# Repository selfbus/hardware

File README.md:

<h2>Deprecation Notice</h2>
Until May 11th 2023 selfbus hardware was split into "hardware" (stable projects) and "hardware-incubation" (dev projects). Since this split constantly lead to confusion mainly because stable hardware was not migrated to "hardware" but also because namings and structures differed between these two repositories, we decided to re-structe both to the same folder structure and merge them. In combination with clear collaboration rules it should be much easier now to understand what can be found where. 
<br/><br/>The newly created repository is located here: https://github.com/selfbus/hardware-merged

<hr/>

<h2>Master-Branch</h2>
This branch contains released Selfbus hardware

The top level directories contain:

<ul>
<li> Apps - applications/devices that require a controller board
<li> Controller - controller boards
<li> Module - devices that do not require a controller board
<li> Misc - other stuff that is not an EIB bus device
</ul>

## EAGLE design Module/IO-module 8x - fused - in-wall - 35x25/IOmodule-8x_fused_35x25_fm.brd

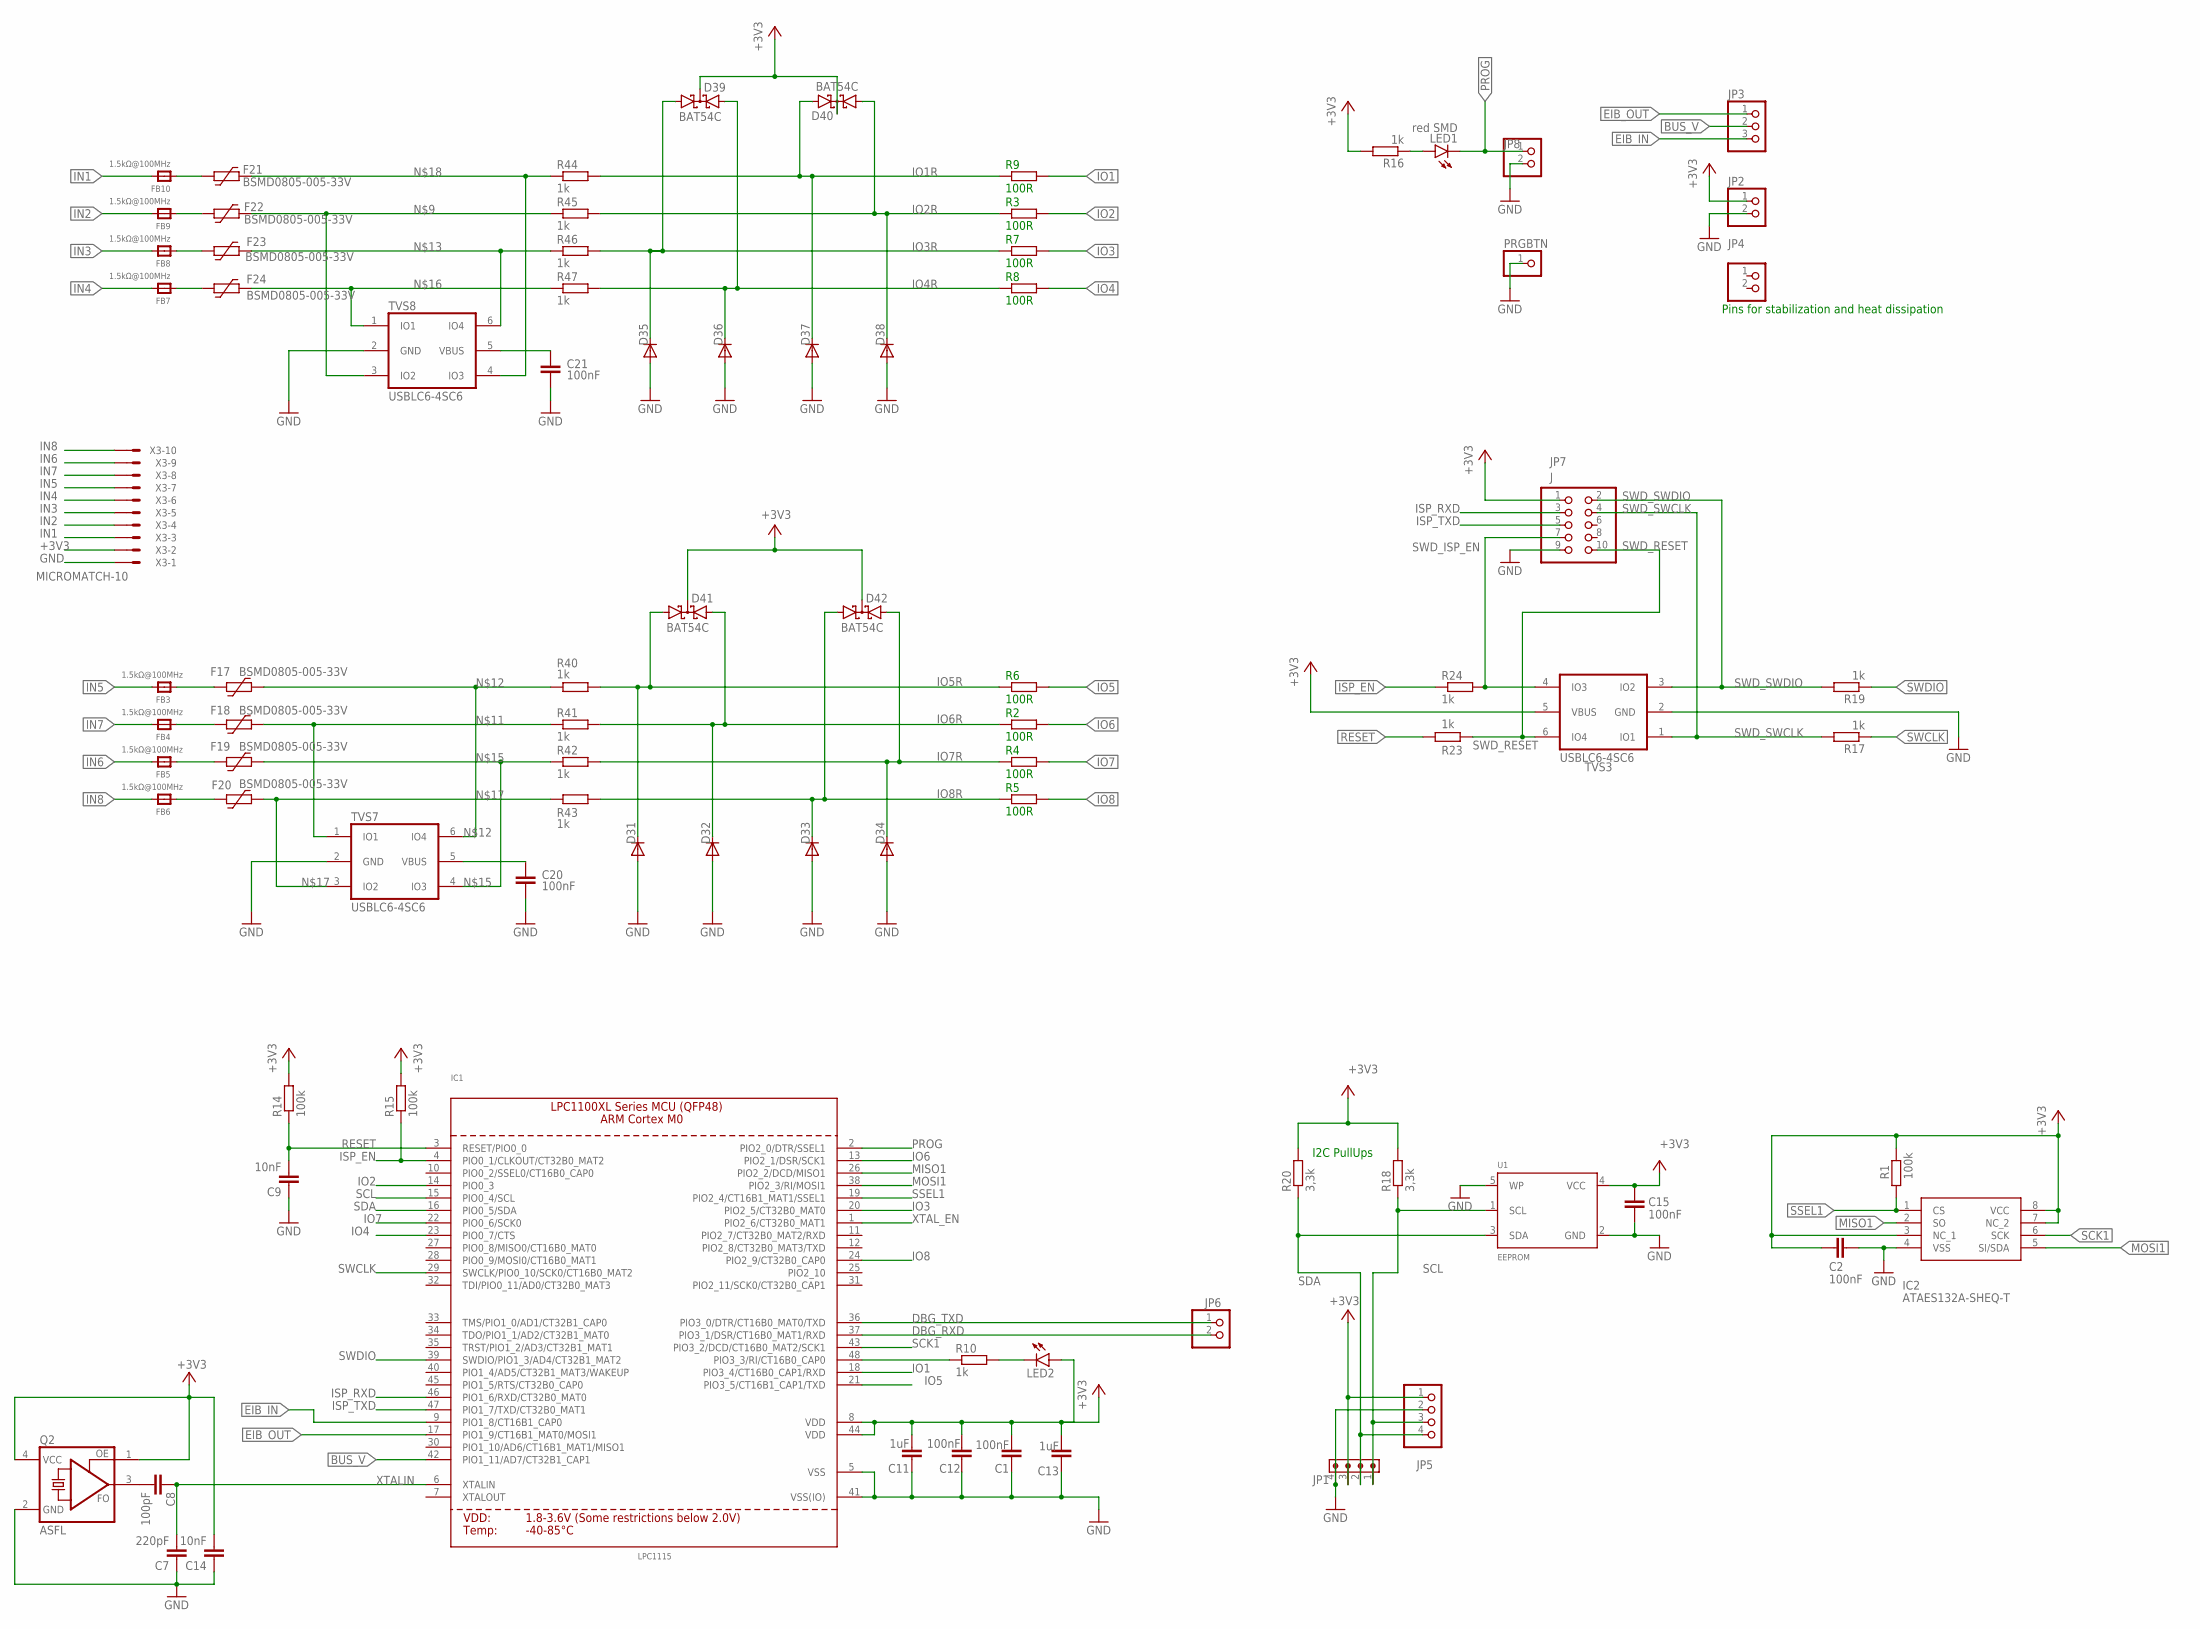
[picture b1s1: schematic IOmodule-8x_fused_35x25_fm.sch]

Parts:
C1, C2, C12, C15, C20, C21: 100nF; C0805
C7: 220pF; C0805
C8: 100pF; C0805
C9, C14: 10nF; C0805
C11, C13: 1uF; C0805
D31, D32, D33, D34, D35, D36, D37, D38: DDZ9684; SOD-123
D39, D40, D41, D42: BAT54C; SOT23
F17, F18, F19, F20, F21, F22, F23, F24: BSMD0805-005-33V; 0805L
FB3, FB4, FB5, FB6, FB7, FB8, FB9, FB10: 1.5kΩ@100MHz; 0805
IC1: LPC1115; LQFP48
IC2: ATAES132A-SHEQ-T; SOIC127P600X175-8N
JP1: 62000411622
JP2, JP4, JP6, JP8: PINHD-1X2; 1X02
JP3: PINHD-1X3; 1X03
JP5: PINHD-1X4; 1X04
JP7: J; 2X05M
LED1: red SMD; CHIPLED_0805
LED2: LEDCHIPLED_0805; CHIPLED_0805
PRGBTN: PINHD-1X1; 1X01
Q2: ASFL; ASF
R1, R14, R15: 100k; R0805
R2, R3, R4, R5, R6, R7, R8, R9: 100R; R0805
R10, R16, R17, R19, R23, R24, R40, R41, R42, R43, R44, R45, R46, R47: 1k; R0805
R18, R20: 3,3k; R0805
TVS3, TVS7, TVS8: USBLC6-4SC6; SOT-23-6L
U1: EEPROM; SOT23-5
X3: MICROMATCH-10

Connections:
+3V3: C1.2, C2.1, C11.2, C12.2, C13.2, C14.2, C15.1, D39.3 (CC), D40.3 (CC), D41.3 (CC), D42.3 (CC), IC1.8 (VDD), IC1.44 (VDD), IC2.3 (NC_1), IC2.7 (NC_2), IC2.8 (VCC), JP1.3, JP2.1, JP5.1, JP7.1, LED2.A, Q2.1 (OE), Q2.4 (VCC), R1.2, R14.2, R15.2, R16.2, R18.2, R20.2, TVS3.5 (VBUS), U1.4 (VCC), X3.2
BUS_V: IC1.42 (PIO1_11/AD7/CT32B1_CAP1), JP3.2
DBG_RXD: IC1.37 (PIO3_1/DSR/CT16B0_MAT1/RXD), JP6.2
DBG_TXD: IC1.36 (PIO3_0/DTR/CT16B0_MAT0/TXD), JP6.1
EIB_IN: IC1.9 (PIO1_8/CT16B1_CAP0), JP3.3
EIB_OUT: IC1.17 (PIO1_9/CT16B1_MAT0/MOSI1), JP3.1
GND: C1.1, C2.2, C7.1, C9.1, C11.1, C12.1, C13.1, C14.1, C15.2, C20.1, C21.1, D31.A, D32.A, D33.A, D34.A, D35.A, D36.A, D37.A, D38.A, IC1.5 (VSS), IC1.41 (VSS(IO)), IC2.4 (VSS), JP1.4, JP2.2, JP5.2, JP7.9, JP8.2, PRGBTN.1, Q2.2 (GND), TVS3.2 (GND), TVS7.2 (GND), TVS8.2 (GND), U1.2 (GND), U1.5 (WP), X3.1
IN1: FB10.2, X3.3
IN2: FB9.2, X3.4
IN3: FB8.2, X3.5
IN4: FB7.2, X3.6
IN5: FB3.2, X3.7
IN6: FB5.2, X3.9
IN7: FB4.2, X3.8
IN8: FB6.2, X3.10
IO1: IC1.18 (PIO3_4/CT16B0_CAP1/RXD), R9.2
IO1R: D37.C, D40.2 (A2), R9.1, R44.2
IO2: IC1.14 (PIO0_3), R3.2
IO2R: D38.C, D40.1 (A1), R3.1, R45.2
IO3: IC1.20 (PIO2_5/CT32B0_MAT0), R7.2
IO3R: D35.C, D39.1 (A1), R7.1, R46.2
IO4: IC1.23 (PIO0_7/CTS), R8.2
IO4R: D36.C, D39.2 (A2), R8.1, R47.2
IO5: IC1.21 (PIO3_5/CT16B1_CAP1/TXD), R6.2
IO5R: D31.C, D41.1 (A1), R6.1, R40.2
IO6: IC1.13 (PIO2_1/DSR/SCK1), R2.2
IO6R: D32.C, D41.2 (A2), R2.1, R41.2
IO7: IC1.22 (PIO0_6/SCK0), R4.2
IO7R: D34.C, D42.2 (A2), R4.1, R42.2
IO8: IC1.24 (PIO2_9/CT32B0_CAP0), R5.2
IO8R: D33.C, D42.1 (A1), R5.1, R43.2
ISP_EN: IC1.4 (PIO0_1/CLKOUT/CT32B0_MAT2), R15.1, R24.1
ISP_RXD: IC1.46 (PIO1_6/RXD/CT32B0_MAT0), JP7.3
ISP_TXD: IC1.47 (PIO1_7/TXD/CT32B0_MAT1), JP7.5
MISO1: IC1.26 (PIO2_2/DCD/MISO1), IC2.2 (SO)
MOSI1: IC1.38 (PIO2_3/RI/MOSI1), IC2.5 (SI/SDA)
unnamed: F19.1, FB5.1
unnamed: F20.1, FB6.1
unnamed: F18.1, FB4.1
unnamed: F17.1, FB3.1
unnamed: F24.1, FB7.1
unnamed: F23.1, FB8.1
unnamed: F21.1, FB10.1
unnamed: F22.1, FB9.1
unnamed: F22.2, R45.1, TVS8.3 (IO2)
unnamed: C8.2, Q2.3 (FO)
unnamed: F18.2, R41.1, TVS7.1 (IO1)
unnamed: F17.2, R40.1, TVS7.6 (IO4)
unnamed: F23.2, R46.1, TVS8.6 (IO4)
unnamed: LED2.C, R10.2
unnamed: F19.2, R42.1, TVS7.4 (IO3)
unnamed: F24.2, R47.1, TVS8.1 (IO1)
unnamed: F20.2, R43.1, TVS7.3 (IO2)
unnamed: F21.2, R44.1, TVS8.4 (IO3)
unnamed: IC1.48 (PIO3_3/RI/CT16B0_CAP0), R10.1
unnamed: LED1.A, R16.1
unnamed: C20.2, TVS7.5 (VBUS)
unnamed: C21.2, TVS8.5 (VBUS)
PROG: IC1.2 (PIO2_0/DTR/SSEL1), JP8.1, LED1.C
RESET: C9.2, IC1.3 (RESET/PIO0_0), R14.1, R23.2
SCK1: IC1.43 (PIO3_2/DCD/CT16B0_MAT2/SCK1), IC2.6 (SCK)
SCL: IC1.15 (PIO0_4/SCL), JP1.1, JP5.3, R18.1, U1.1 (SCL)
SDA: IC1.16 (PIO0_5/SDA), JP1.2, JP5.4, R20.1, U1.3 (SDA)
SSEL1: IC1.19 (PIO2_4/CT16B1_MAT1/SSEL1), IC2.1 (CS), R1.1
SWCLK: IC1.29 (SWCLK/PIO0_10/SCK0/CT16B0_MAT2), R17.1
SWDIO: IC1.39 (SWDIO/PIO1_3/AD4/CT32B1_MAT2), R19.1
SWD_ISP_EN: JP7.7, R24.2, TVS3.4 (IO3)
SWD_RESET: JP7.10, R23.1, TVS3.6 (IO4)
SWD_SWCLK: JP7.4, R17.2, TVS3.1 (IO1)
SWD_SWDIO: JP7.2, R19.2, TVS3.3 (IO2)
XTALIN: C7.2, C8.1, IC1.6 (XTALIN)
XTAL_EN: IC1.1 (PIO2_6/CT32B0_MAT1)

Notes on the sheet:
I2C PullUps
Pins for stabilization and heat dissipation

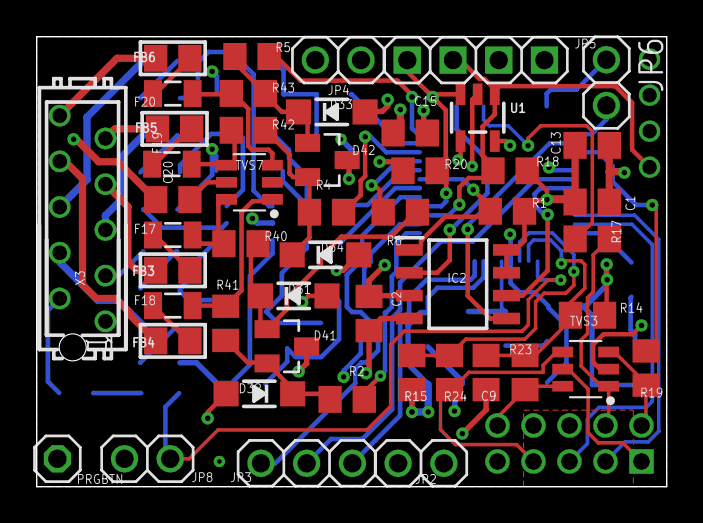
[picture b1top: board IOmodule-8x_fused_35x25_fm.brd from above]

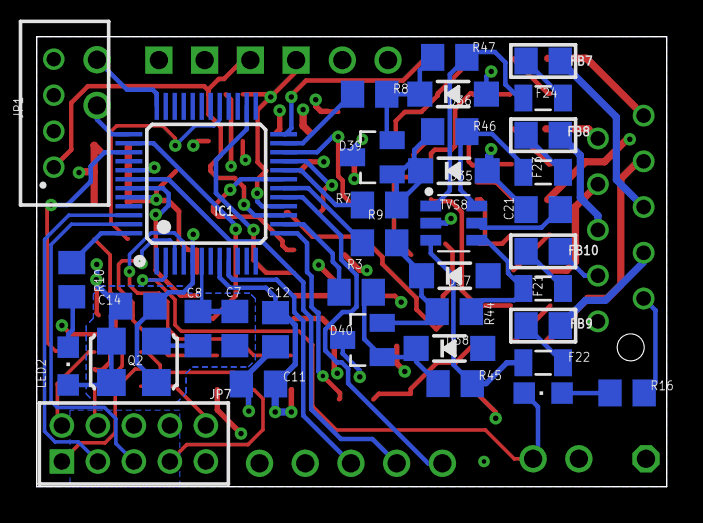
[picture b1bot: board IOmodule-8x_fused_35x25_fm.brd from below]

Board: 4 copper layers, 35.0 x 25.0 mm, 86 parts (37 on the bottom side), 71 nets.

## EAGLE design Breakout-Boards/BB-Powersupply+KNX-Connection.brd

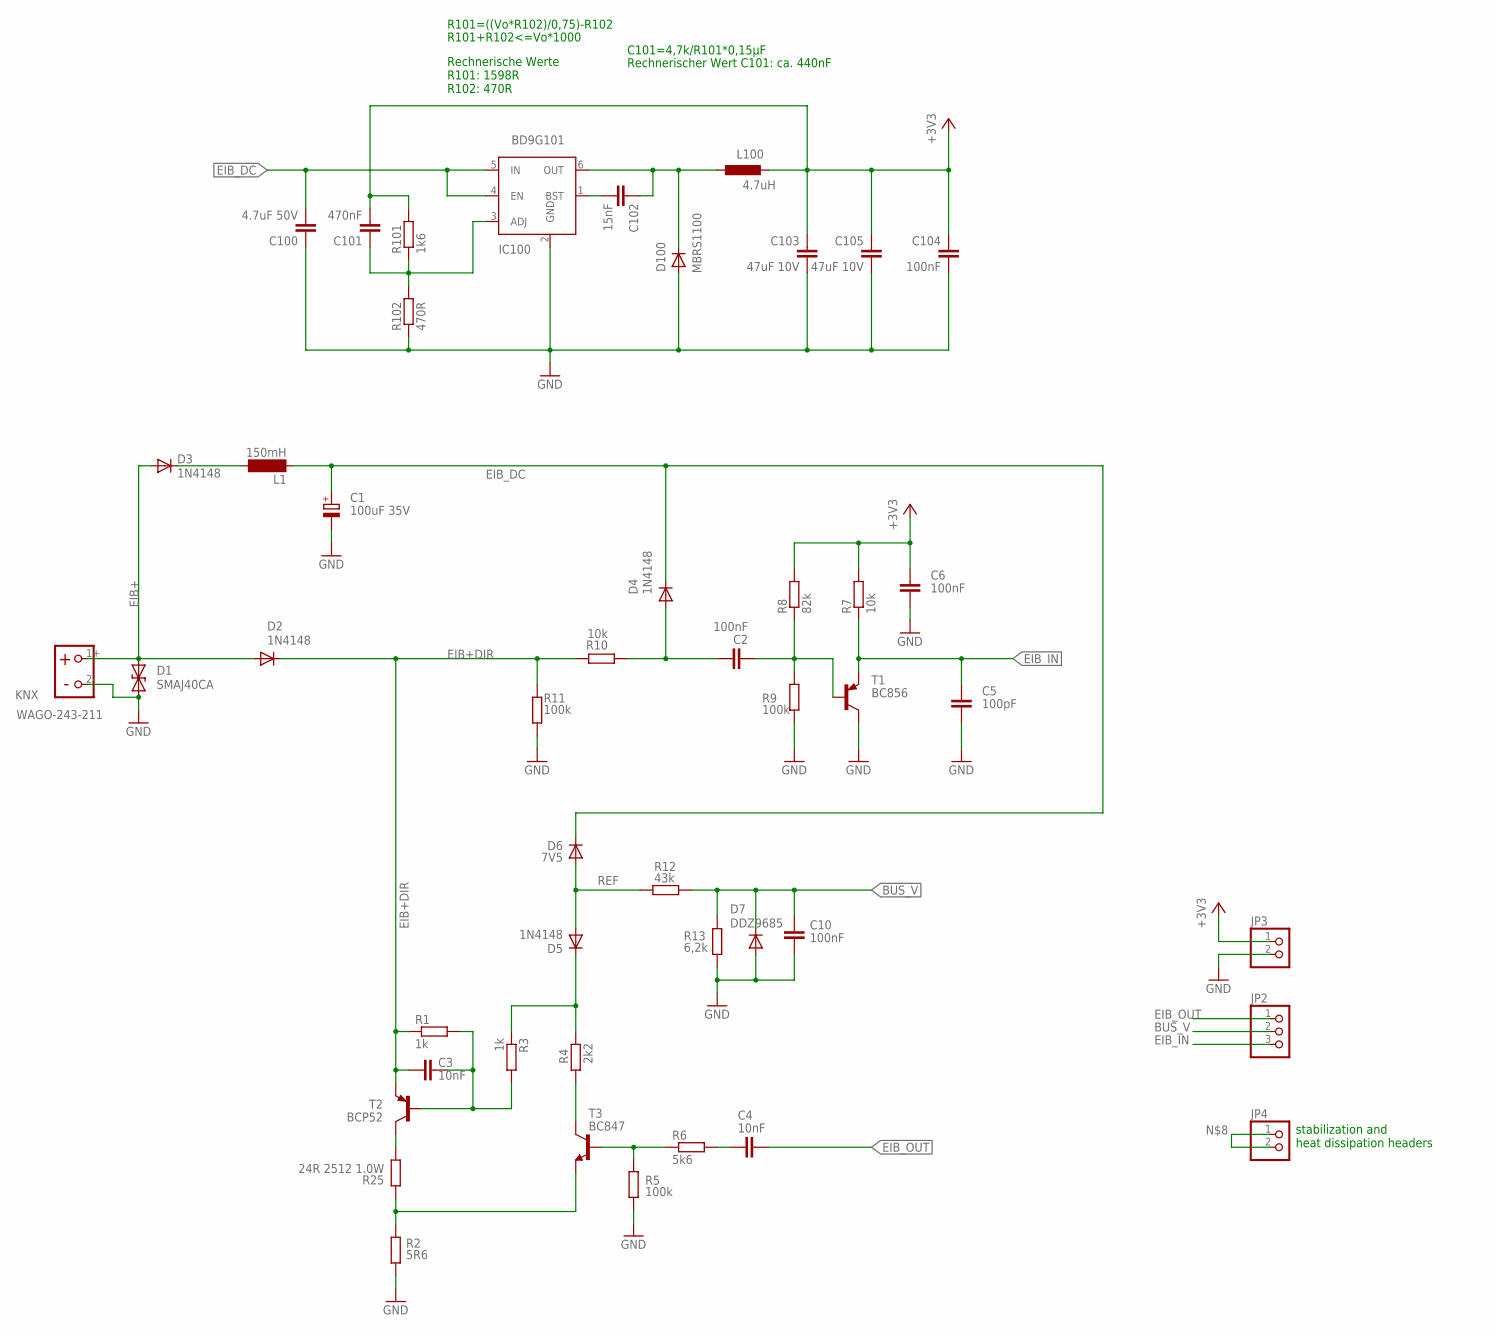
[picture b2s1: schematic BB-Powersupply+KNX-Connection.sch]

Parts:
C1: 100uF 35V; SANYO-OSCON_SMD_C6
C2, C6, C10, C104: 100nF; C0805
C3, C4: 10nF; C0805
C5: 100pF; C0805
C100: 4.7uF 50V; C0805
C101: 470nF; C0805
C102: 15nF; C0805
C103, C105: 47uF 10V; C0805
D1: SMAJ40CA; DO214AC
D2, D3, D4, D5: 1N4148; SOD-123
D6: 7V5; SOD-123
D7: DDZ9685; SOD-123
D100: MBRS1100; SOD-123
IC100: BD9G101; SOT23-6
JP2: PINHD-1X3; 1X03
JP3, JP4: PINHD-1X2; 1X02
KNX: WAGO-243-211
L1: 150mH; BS11
L100: 4.7uH; L4532P
R1, R3: 1k; R0805
R2: 5R6; R0805
R4: 2k2; R0805
R5, R9, R11: 100k; R0805
R6: 5k6; R0805
R7, R10: 10k; R0805
R8: 82k; R0805
R12: 43k; R0805
R13: 6,2k; R0805
R25: 24R 2512 1.0W; R2512
R101: 1k6; R0805
R102: 470R; R0805
T1: BC856; SOT23-BEC
T2: BCP52; SOT223
T3: BC847; SOT23

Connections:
+3V3: C6.2, C101.2, C103.1, C104.1, C105.1, JP3.1, L100.2, R7.2, R8.2, R101.2
BST: C102.2, IC100.1 (BST)
BUS_V: C10.2, D7.C, JP2.2, R12.2, R13.1
EIB+: D1.C (2), D2.A, D3.A, KNX.1+
EIB+DIR: C3.1, D2.C, R1.1, R10.2, R11.2, T2.3 (E)
EIB_DC: C1.+, C100.2, D4.C, D6.C, IC100.4 (EN), IC100.5 (IN), L1.1
EIB_IN: C5.2, JP2.3, R7.1, T1.E
EIB_OUT: C4.2, JP2.1
FB: C101.1, IC100.3 (ADJ), R101.1, R102.2
GND: C1.-, C5.1, C6.1, C10.1, C100.1, C103.2, C104.2, C105.2, D1.A (1), D7.A, D100.A, IC100.2 (GND), JP3.2, KNX.2-, R2.1, R5.2, R9.1, R11.1, R13.2, R102.1, T1.C
LX: C102.1, D100.C, IC100.6 (OUT), L100.1
unnamed: C2.2, D4.A, R10.1
unnamed: D3.C, L1.2
unnamed: C4.1, R6.2
unnamed: R4.1, T3.3 (C)
unnamed: R2.2, R25.1, T3.2 (E)
unnamed: JP4.1, JP4.2, R25.2, T2.2 (C), T2.4 (C)
unnamed: R5.1, R6.1, T3.1 (B)
unnamed: C2.1, R8.1, R9.2, T1.B
unnamed: C3.2, R1.2, R3.2, T2.1 (B)
unnamed: D5.C, R3.1, R4.2
REF: D5.A, D6.A, R12.1

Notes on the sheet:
R101=((Vo*R102)/0,75)-R102
R101+R102<=Vo*1000
Rechnerische Werte R101: 1598R R102: 470R
C101=4,7k/R101*0,15µF
Rechnerischer Wert C101: ca. 440nF
stabilization and heat dissipation headers

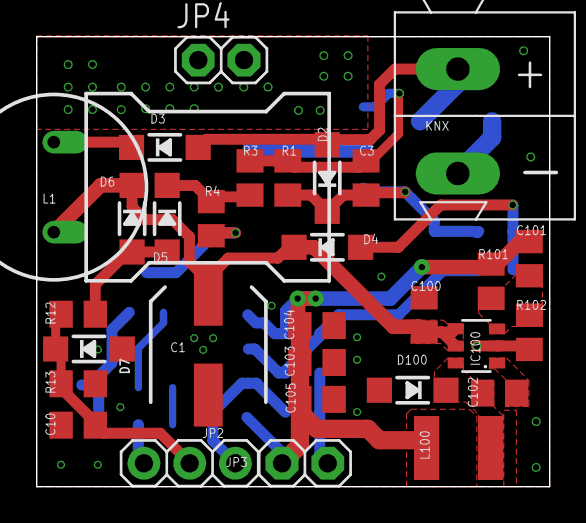
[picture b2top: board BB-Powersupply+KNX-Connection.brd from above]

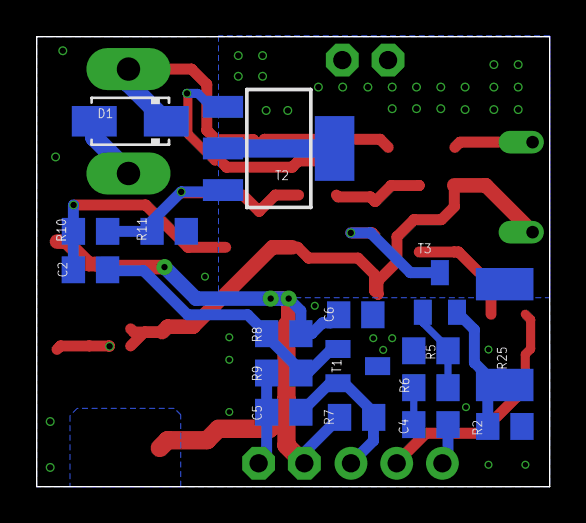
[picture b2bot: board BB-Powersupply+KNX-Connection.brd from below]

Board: 2 copper layers, 28.5 x 25.0 mm, 47 parts (17 on the bottom side), 22 nets.

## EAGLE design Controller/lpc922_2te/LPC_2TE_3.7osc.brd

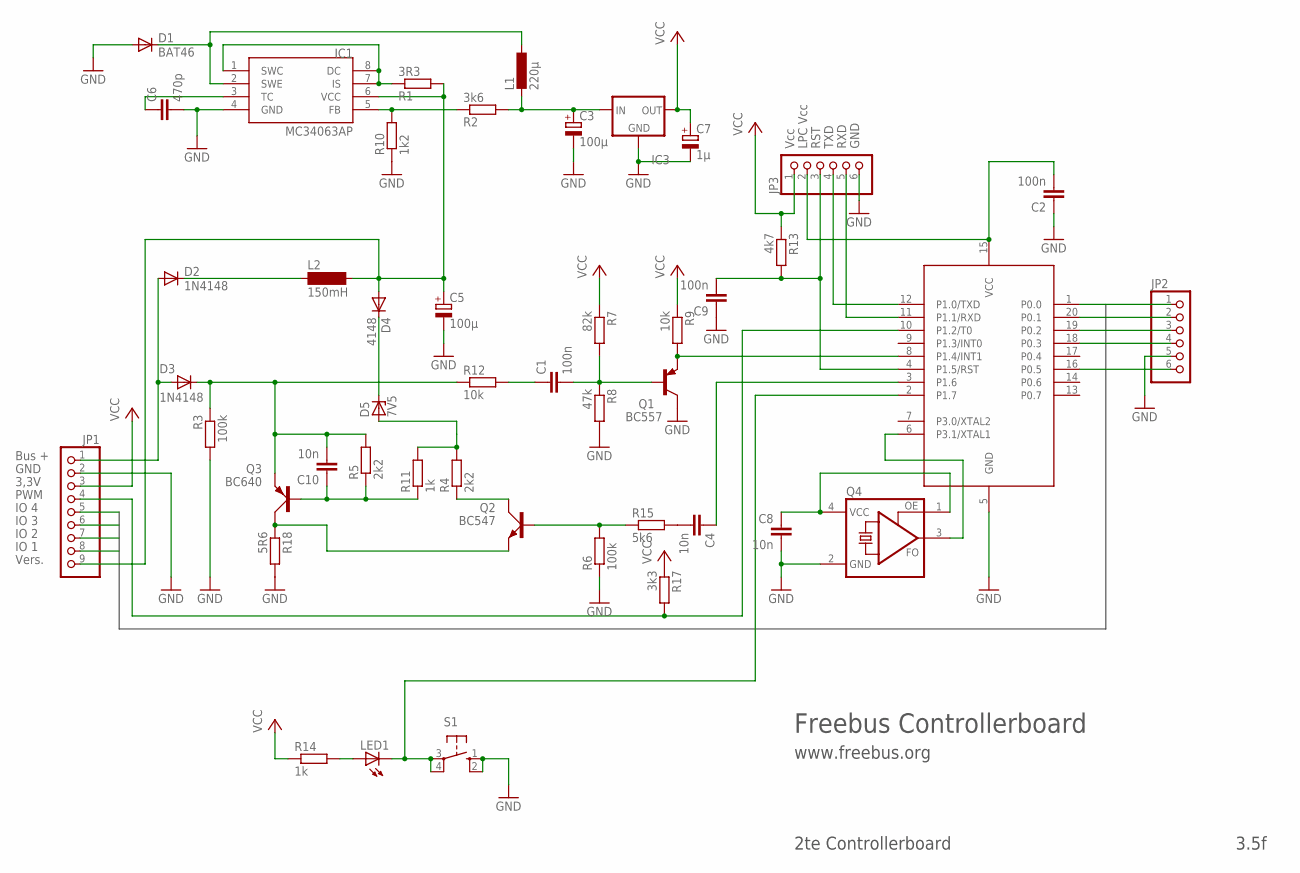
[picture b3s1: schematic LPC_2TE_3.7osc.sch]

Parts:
89LPC922: 89LPC922; DIL20
C1, C2, C9: 100n; C025-024X044
C3: 100µ; E2,5-6
C4, C10: 10n; C025-024X044
C5: 100µ; E3,5-8
C6: 470p; C025-024X044
C7: 1µ; E2-5
C8: 10n; C1206
D1: BAT46; DO34-7
D2: 1N4148; D-2.5
D3: 1N4148; DO35-S
D4: 4148; D-2.5
D5: 7V5; ZDIODE
IC1: MC34063AP; DIL08
IC3: 79LXX
JP1: PINHD-1X9; 1X09
JP2, JP3: PINHD-1X6; 1X06
L1: 220µ; 0207/12
L2: 150mH; BS11
LED1: LED3MM
Q1: BC557; TO92
Q2: BC547; SOT54A
Q3: BC640; SOT54D
Q4: ASFL1; ASF
R1: 3R3; 0207/7
R2: 3k6; 0207/7
R3, R6: 100k; 0207/2V
R4, R5: 2k2; 0207/2V
R7: 82k; 0207/2V
R8: 47k; 0207/2V
R9, R12: 10k; 0207/2V
R10: 1k2; 0207/7
R11, R14: 1k; 0207/2V
R13: 4k7; 0207/2V
R15: 5k6; 0207/2V
R17: 3k3; 0207/2V
R18: 5R6; 0207/2V
S1: 10-XX; B3F-10XX

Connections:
/RESET: 89LPC922.4 (P1.5/RST), C9.2, JP3.3, R13.2
BASE: C1.2, Q1.2 (B), R7.2, R8.1
EIB+: D2.A, D3.P$1 (A), JP1.1
FETGATE: Q2.B, R6.2, R15.1
GND: 89LPC922.5 (GND), C2.1, C3.-, C5.-, C6.2, C7.-, C8.2, C9.1, D1.A, IC1.4 (GND), IC3.GND, JP1.2, JP2.5, JP3.6, Q1.3 (C), Q4.2 (GND), R3.2, R6.1, R8.2, R10.1, R18.2, S1.1 (S), S1.2 (S1)
unnamed: Q2.C, R4.1
unnamed: C8.1, Q4.1 (OE), Q4.4 (VCC)
unnamed: C10.2, D3.P$2 (B), Q3.E, R3.1, R5.2, R12.1
unnamed: 89LPC922.3 (P1.6), C4.1
unnamed: 89LPC922.6 (P3.1/XTAL1), Q4.3 (FO)
unnamed: 89LPC922.2 (P1.7), LED1.K (C), S1.3, S1.4 (P1)
unnamed: IC1.1 (SWC), IC1.7 (IS), IC1.8 (DC), R1.1
unnamed: LED1.A, R14.2
unnamed: C5.+, D4.A, IC1.6 (VCC), JP1.9, L2.2, R1.2
unnamed: IC1.5 (FB), R2.1, R10.2
unnamed: D1.C, IC1.2 (SWE), L1.1
unnamed: D2.C, L2.1
unnamed: C6.1, IC1.3 (TC)
unnamed: D4.C, D5.C
unnamed: C1.1, R12.2
unnamed: C4.2, R15.2
unnamed: Q2.E, Q3.C, R18.1
unnamed: C3.+, IC3.IN, L1.2, R2.2
unnamed: D5.A, R4.2, R11.2
unnamed: C10.1, Q3.B, R5.1, R11.1
unnamed: 89LPC922.12 (P1.0/TXD), JP3.4
unnamed: 89LPC922.11 (P1.1/RXD), JP3.5
unnamed: 89LPC922.15 (VCC), C2.2, JP3.2
P0.0: 89LPC922.1 (P0.0), JP1.8, JP2.1
P0.1: 89LPC922.20 (P0.1), JP1.7, JP2.2
P0.2: 89LPC922.19 (P0.2), JP1.6, JP2.3
P0.3: 89LPC922.18 (P0.3), JP1.5, JP2.4
P0.5: 89LPC922.16 (P0.5), JP2.6
PWM: 89LPC922.10 (P1.2/T0), JP1.4, R17.2
SIGIN: 89LPC922.8 (P1.4/INT1), Q1.1 (E), R9.2
VCC: C7.+, IC3.OUT, JP1.3, JP3.1, R7.1, R9.1, R13.1, R14.1, R17.1

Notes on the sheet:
Bus +
GND
3,3V
PWM
IO 1
IO 2
IO 3
IO 4
Vcc
LPC Vcc
RST
TXD
RXD
Vers.
Freebus Controllerboard
www.freebus.org
2te Controllerboard
3.5f

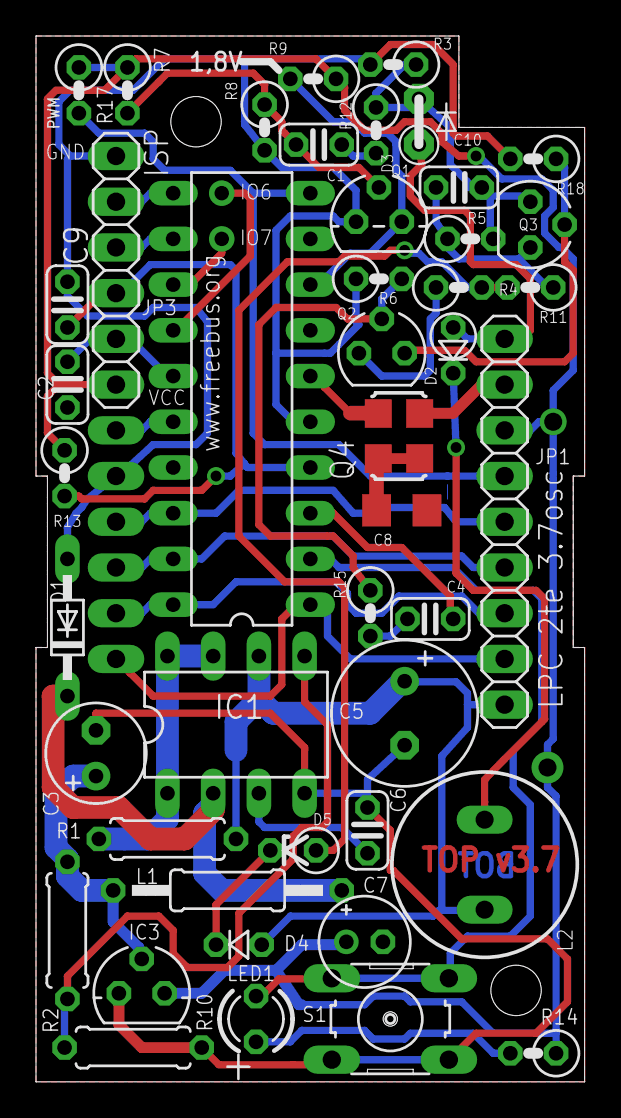
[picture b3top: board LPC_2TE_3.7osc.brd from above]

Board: 2 copper layers, 30.5 x 58.1 mm, 46 parts (1 on the bottom side), 36 nets.

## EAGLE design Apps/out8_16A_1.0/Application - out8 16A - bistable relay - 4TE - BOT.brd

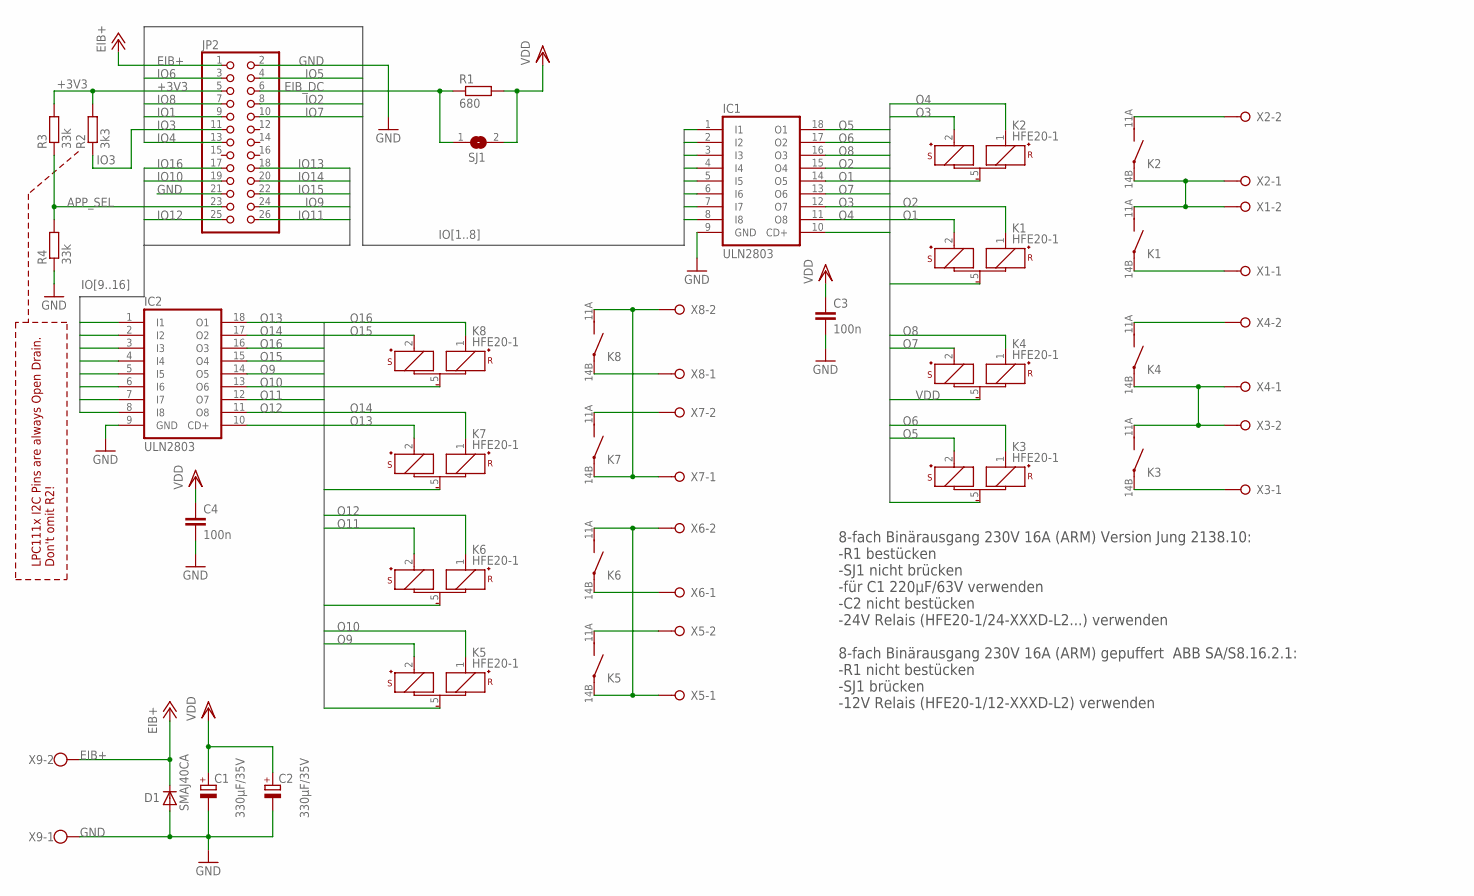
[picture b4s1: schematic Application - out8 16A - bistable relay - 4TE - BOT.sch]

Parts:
C1, C2: 330µF/35V; E3,5-8
C3, C4: 100n; C1206
D1: SMAJ40CA; SMB
IC1, IC2: ULN2803; SO18W
JP2: A; 2X13SMD
K1, K2, K3, K4, K5, K6, K7, K8: HFE20-1; HFE20-3-504
R1: 680; M1206
R2: 3k3; M1206
R3, R4: 33k; M1206
SJ1: A; SJ
X1, X2, X3, X4, X5, X6, X7, X8: W237-02P; W237-132
X9: W237-102

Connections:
+3V3: JP2.5, R2.2, R3.2
APP_SEL: JP2.23, R3.1, R4.2
EIB+: D1.1 (C), JP2.1, X9.2
EIB_DC: JP2.6, R1.1, SJ1.1
GND: C1.-, C2.-, C3.2, C4.2, D1.2 (A), IC1.9 (GND), IC2.9 (GND), JP2.2, JP2.21, R4.1, X9.1
IO1: IC1.5 (I5), JP2.9
IO2: IC1.4 (I4), JP2.8
IO3: IC1.7 (I7), JP2.11, R2.1
IO4: IC1.8 (I8), JP2.13
IO5: IC1.1 (I1), JP2.4
IO6: IC1.2 (I2), JP2.3
IO7: IC1.6 (I6), JP2.10
IO8: IC1.3 (I3), JP2.7
IO9: IC2.5 (I5), JP2.24
IO10: IC2.6 (I6), JP2.19
IO11: IC2.7 (I7), JP2.26
IO12: IC2.8 (I8), JP2.25
IO13: IC2.1 (I1), JP2.18
IO14: IC2.2 (I2), JP2.20
IO15: IC2.4 (I4), JP2.22
IO16: IC2.3 (I3), JP2.17
K12: K1.11A (PB), K2.14B (PA), X1.2, X2.1
K34: K3.11A (PB), K4.14B (PA), X3.2, X4.1
K56: K5.14B (PA), K6.11A (PB), X5.1, X6.2
K78: K7.14B (PA), K8.11A (PB), X7.1, X8.2
unnamed: K4.11A (PB), X4.2
unnamed: K8.14B (PA), X8.1
unnamed: K1.14B (PA), X1.1
unnamed: K3.14B (PA), X3.1
unnamed: K2.11A (PB), X2.2
unnamed: K7.11A (PB), X7.2
unnamed: K5.11A (PB), X5.2
unnamed: K6.14B (PA), X6.1
O1: IC1.14 (O5), K1.2 (S+)
O2: IC1.15 (O4), K1.1 (R+)
O3: IC1.12 (O7), K2.2 (S+)
O4: IC1.11 (O8), K2.1 (R+)
O5: IC1.18 (O1), K3.2 (S+)
O6: IC1.17 (O2), K3.1 (R+)
O7: IC1.13 (O6), K4.2 (S+)
O8: IC1.16 (O3), K4.1 (R+)
O9: IC2.14 (O5), K5.2 (S+)
O10: IC2.13 (O6), K5.1 (R+)
O11: IC2.12 (O7), K6.2 (S+)
O12: IC2.11 (O8), K6.1 (R+)
O13: IC2.18 (O1), K7.2 (S+)
O14: IC2.17 (O2), K7.1 (R+)
O15: IC2.15 (O4), K8.2 (S+)
O16: IC2.16 (O3), K8.1 (R+)
VDD: C1.+, C2.+, C3.1, C4.1, IC1.10 (CD+), IC2.10 (CD+), K1.5 (-), K2.5 (-), K3.5 (-), K4.5 (-), K5.5 (-), K6.5 (-), K7.5 (-), K8.5 (-), R1.2, SJ1.2

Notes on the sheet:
8-fach Binärausgang 230V 16A (ARM) Version Jung 2138.10: -R1 bestücken -SJ1 nicht brücken -für C1 220µF/63V verwenden -C2 nicht bestücken -24V Relais (HFE20-1/24-XXXD-L2...) verwenden 8-fach Binärausgang 230V 16A (ARM) gepuffert ABB SA/S8.16.2.1: -R1 nicht bestücken -SJ1 brücken -12V Relais (HFE20-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
LPC111x I2C Pins are always Open Drain. Don't omit R2!

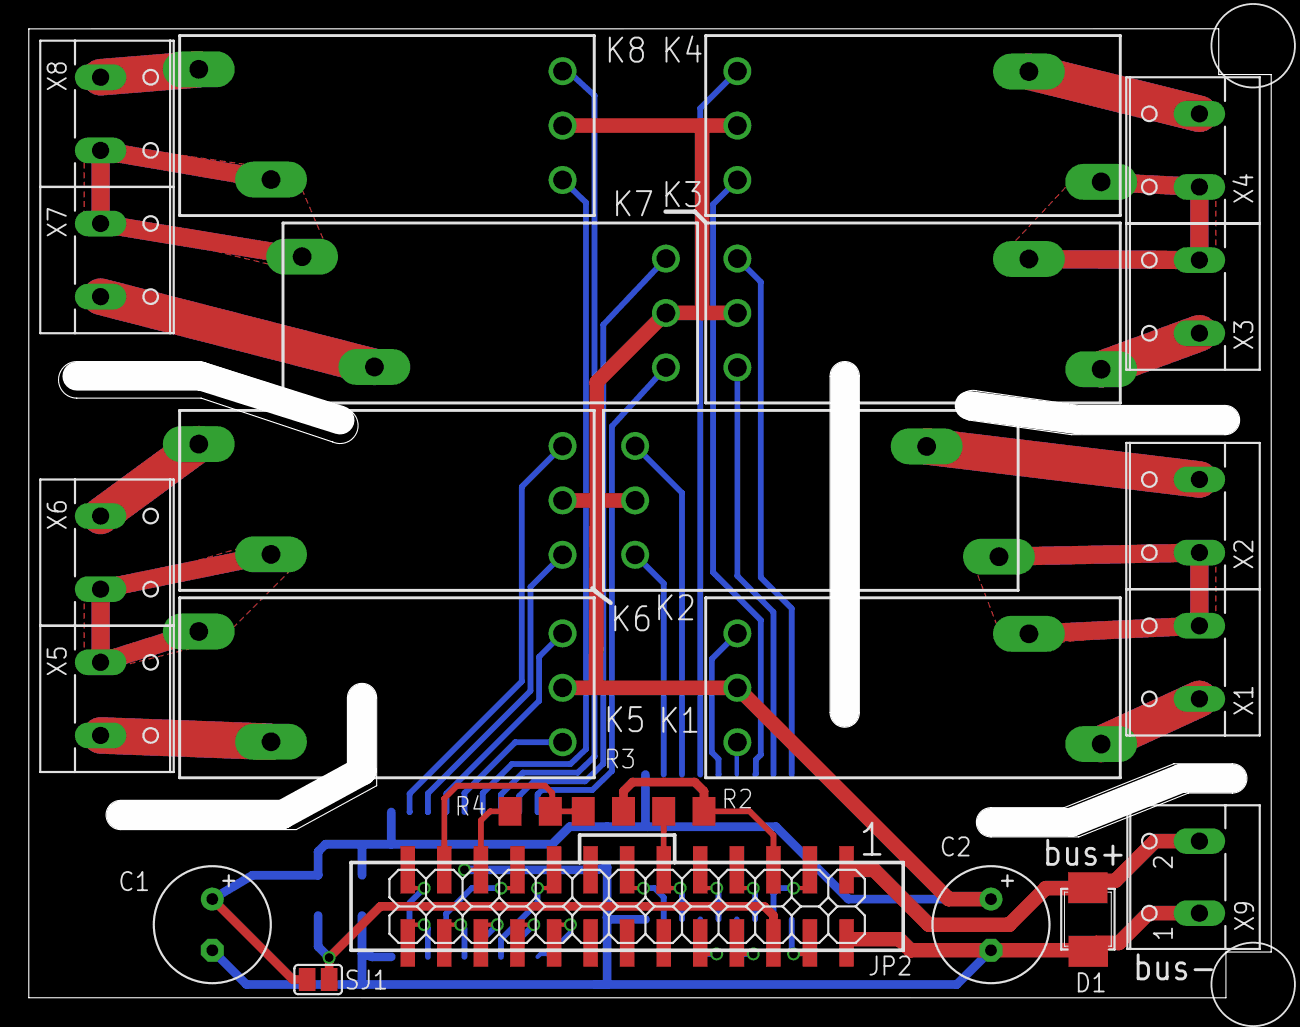
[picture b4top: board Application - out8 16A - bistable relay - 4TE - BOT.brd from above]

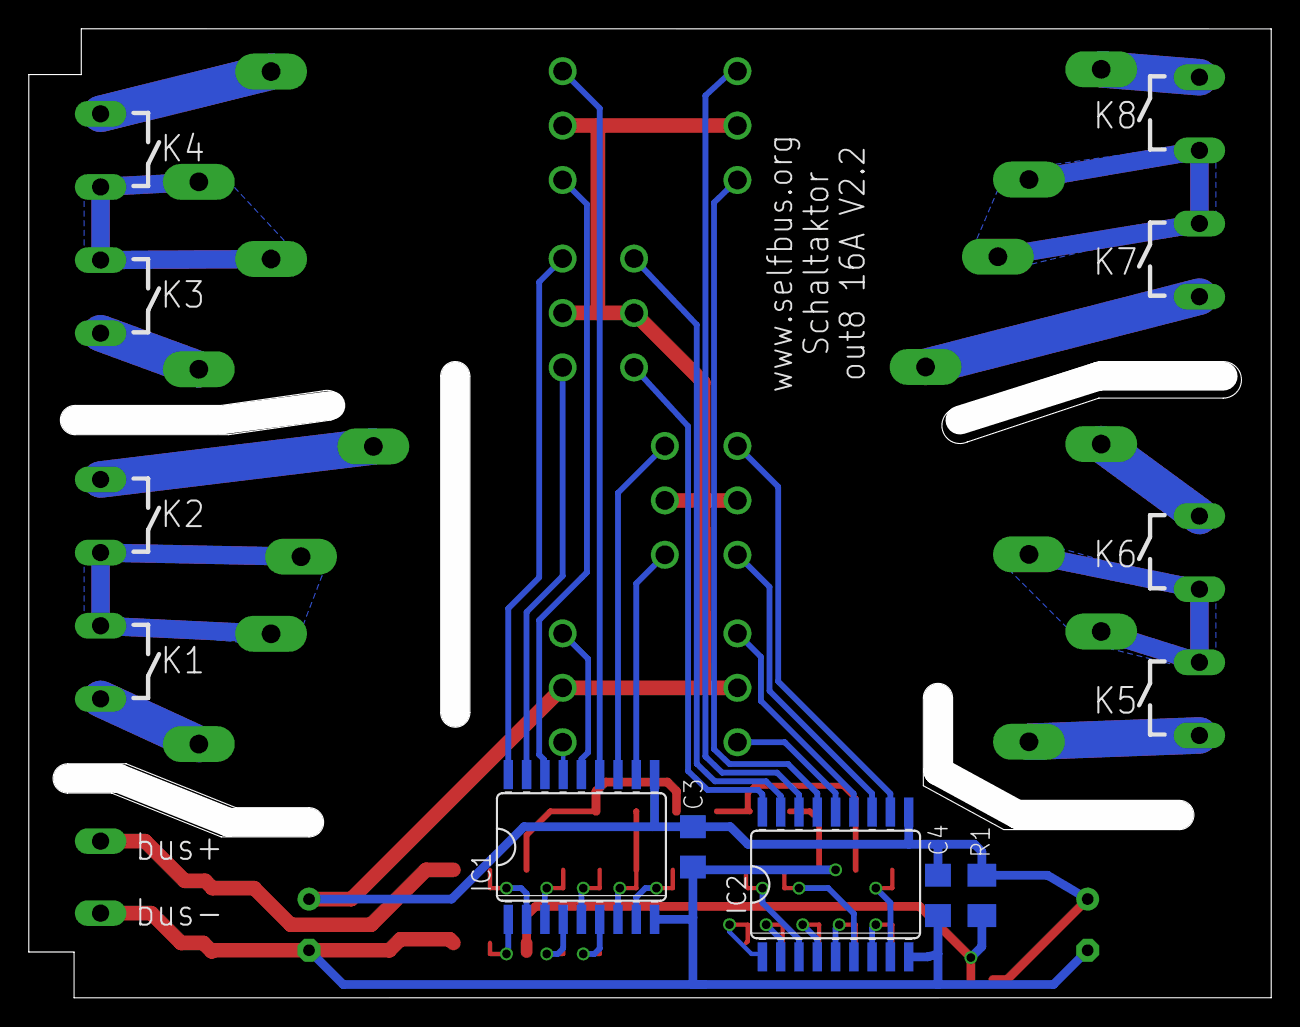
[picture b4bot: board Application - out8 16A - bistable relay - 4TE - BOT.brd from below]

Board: 2 copper layers, 86.3 x 67.3 mm, 31 parts (5 on the bottom side), 50 nets.

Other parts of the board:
U$1: HUT4C-NO-DRILL

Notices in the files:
parts and their libraries:
microbuilder: This work is placed in the public domain, and may be freely used for commercial and non-commercial work with the following conditions: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
Eagle_WR-WTB: Copyright: Würth Elektronik
